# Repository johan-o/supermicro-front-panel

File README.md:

# supermicro-front-panel
A simple KiCad project to break out a Supermicro motherboard header into its corresponding ATX pinout.

## BOM / Parts List

| Count | Part |
| --- | --- |
| 6 | 0805 SMD LEDs | 
| 1 | 2x5 2.54mm vertical pin header, male | 
| 1 | 2x10 2.54mm vertical pin header, male | 
| 1 | 2x10 2.54mm vertical pin header, female |

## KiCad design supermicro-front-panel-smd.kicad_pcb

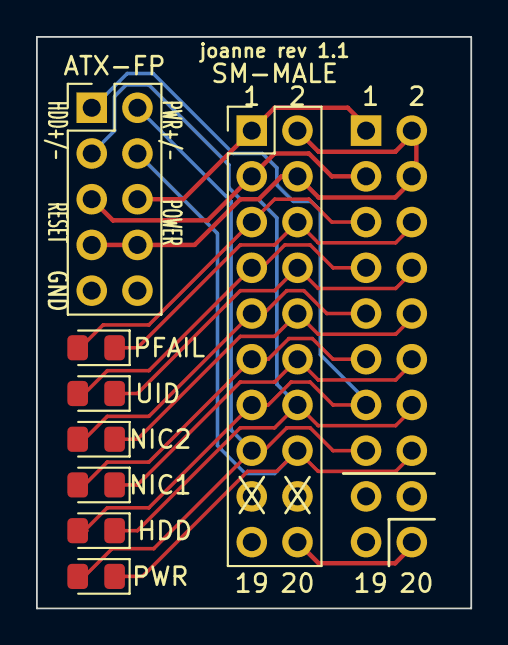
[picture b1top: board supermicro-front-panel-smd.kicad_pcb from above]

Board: 2 copper layers, 24.1 x 31.8 mm, 9 parts (1 on the bottom side), 16 nets.

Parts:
ATX-FP: Conn_02x05_Odd_Even; PinHeader_2x05_P2.54mm_Vertical
HDD: LED; LED_0805_2012Metric_Pad1.15x1.40mm_HandSolder
NIC1, NIC2: LED; LED_0805_2012Metric_Pad1.15x1.40mm_HandSolder
PFAIL: LED; LED_0805_2012Metric_Pad1.15x1.40mm_HandSolder
PWR: LED; LED_0805_2012Metric_Pad1.15x1.40mm_HandSolder
SM-FEMALE: Conn_02x10_Odd_Even; PinSocket_2x10_P2.54mm_Vertical
SM-MALE: Header_02x10_Odd_Even; PinHeader_2x10_P2.54mm_Vertical
UID: LED; LED_0805_2012Metric_Pad1.15x1.40mm_HandSolder

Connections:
/HDD_LED+: ATX-FP.1, HDD.2 (A), SM-FEMALE.13, SM-MALE.13
/HDD_LED-: ATX-FP.3, HDD.1 (K), SM-FEMALE.14, SM-MALE.14
/NIC1_LED+: NIC1.2 (A), SM-FEMALE.11, SM-MALE.11
/NIC1_LED-: NIC1.1 (K), SM-FEMALE.12, SM-MALE.12
/NIC2_LED+: NIC2.2 (A), SM-FEMALE.9, SM-MALE.9
/NIC2_LED-: NIC2.1 (K), SM-FEMALE.10, SM-MALE.10
/NMI: SM-FEMALE.20, SM-MALE.20
/PWR_BUTT: ATX-FP.6, SM-FEMALE.1, SM-MALE.1
/PWR_FAIL_LED+: PFAIL.2 (A), SM-FEMALE.5, SM-MALE.5
/PWR_FAIL_LED-: PFAIL.1 (K), SM-FEMALE.6, SM-MALE.6
/PWR_LED+: ATX-FP.2, PWR.2 (A), SM-FEMALE.15, SM-MALE.15
/PWR_LED-: ATX-FP.4, PWR.1 (K), SM-FEMALE.16, SM-MALE.16
/RESET_BUTT: ATX-FP.5, SM-FEMALE.3, SM-MALE.3
/UID_LED+: SM-FEMALE.7, SM-MALE.7, UID.2 (A)
/UID_LED-: SM-FEMALE.8, SM-MALE.8, UID.1 (K)
GND: ATX-FP.7, ATX-FP.8, ATX-FP.9, SM-FEMALE.2, SM-FEMALE.4, SM-MALE.2, SM-MALE.4

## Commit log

2022-12-26 added first rev
2022-12-27 swapped position of male and female headers
2023-08-16 updated with new kicad changes
2023-08-16 removed old backups
